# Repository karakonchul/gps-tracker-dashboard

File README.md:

# GPS Tracker Dashboard

IoT устройство за локализация със S.O.S
---

## Използвани технологии и инструменти

- **Хардуер**  
  - Arduino Nano  
  - SIM868 GSM/GPRS/GNSS модул  
  - SOS бутон
  - DWM 1000

- **Езици и фреймуъркове**  
  - C++ (Arduino скеч)  
  - JavaScript / TypeScript (Next.js + React)  
  - SQL (PostgreSQL)  

- **База данни**  
  - PostgreSQL (v17.2)  

- **Сървър и бекенд**  
  - Next.js (App Router)  
  - Node.js  
  - `pg` (node-postgres) за връзка с PostgreSQL  
  - `mqtt.js` за MQTT интеграция  

- **Фронтенд**  
  - React (вградено в Next.js)  
  - Google Maps JavaScript API  
  - Tailwind CSS за базова стилизация  

- **Реално-време**  
  - MQTT протокол, публичен брокер HiveMQ (wss://broker.hivemq.com:8884/mqtt)  

- **Тунелиране / DevOps**  
  - ngrok v3 (HTTP тунел, TCP тунел)  

---

## Предварителни условия

1. **Arduino IDE** (или друг инструмент за качване на Arduino скеч)  
2. **Node.js & npm**  
3. **PostgreSQL** (локална инсталация или изнесена чрез ngrok)  
4. **ngrok v3** (регистриран акаунт за резервация на субдомейн)  
5. **Google Maps API ключ**  

---
---

## Конфигурация на база данни (PostgreSQL)

1. Създайте база данни `gps_tracker`:
   ```sql
   CREATE DATABASE gps_tracker;

    CREATE TABLE locations (
      id SERIAL PRIMARY KEY,
      device_id VARCHAR(50) NOT NULL,
      latitude DOUBLE PRECISION NOT NULL,
      longitude DOUBLE PRECISION NOT NULL,
      timestamp TIMESTAMP DEFAULT CURRENT_TIMESTAMP
    );
    CREATE TABLE notifications (
      id SERIAL PRIMARY KEY,
      message TEXT NOT NULL,
      created_at TIMESTAMP DEFAULT CURRENT_TIMESTAMP
    );
    CREATE TABLE uwb_readings (
      id SERIAL PRIMARY KEY,
      device_id VARCHAR(50) NOT NULL,
      x DOUBLE PRECISION NOT NULL,
      y DOUBLE PRECISION NOT NULL,
      timestamp TIMESTAMP WITHOUT TIME ZONE DEFAULT CURRENT_TIMESTAMP
    );
## Геозона (Geofence) – проверка на GPS координати
   
    export function isInsideGeofence(
      latitude: number,
      longitude: number,
      centerLat = 42.6977,
      centerLon = 23.3219,
      radiusKm = 1
    ): boolean {
      const toRad = (v: number) => (v * Math.PI) / 180;
      const R = 6371; // Земен радиус в километри
  
    const dLat = toRad(centerLat - latitude);
    const dLon = toRad(centerLon - longitude);
    const a =
      Math.sin(dLat / 2) ** 2 +
      Math.cos(toRad(latitude)) *
        Math.cos(toRad(centerLat)) *
        Math.sin(dLon / 2) ** 2;
    const distance = R * 2 * Math.atan2(Math.sqrt(a), Math.sqrt(1 - a));
  
    return distance <= radiusKm;
  }

**Входни параметри**

-	**latitude, longitude** – GPS координатите на устройството.
-	**centerLat = 42.6977, centerLon = 23.3219** – координатите на центъра на геозоната (по подразбиране София).
- **radiusKm = 1**– радиусът на геозоната в километри (по подразбиране 1 км).
- **Изчисление:**
1.	Преобразуваме ширина и дължина в радиани чрез toRad.
2.	Пресмятаме разликата на ширини dLat = toRad(centerLat – latitude) и дължини dLon = toRad(centerLon – longitude).
3.	Прилагаме Haversine формулата:
 
            a = sin²(dLat/2) 
              + cos(toRad(latitude)) 
              * cos(toRad(centerLat)) 
              * sin²(dLon/2)
          
            distance = R * 2 * atan2(√a, √(1 – a))

  където R = 6371 км е земният радиус.

   4.	Ако distance ≤ radiusKm, функцията връща true (т.е. точката е вътре в геозоната). В противен случай връща false.

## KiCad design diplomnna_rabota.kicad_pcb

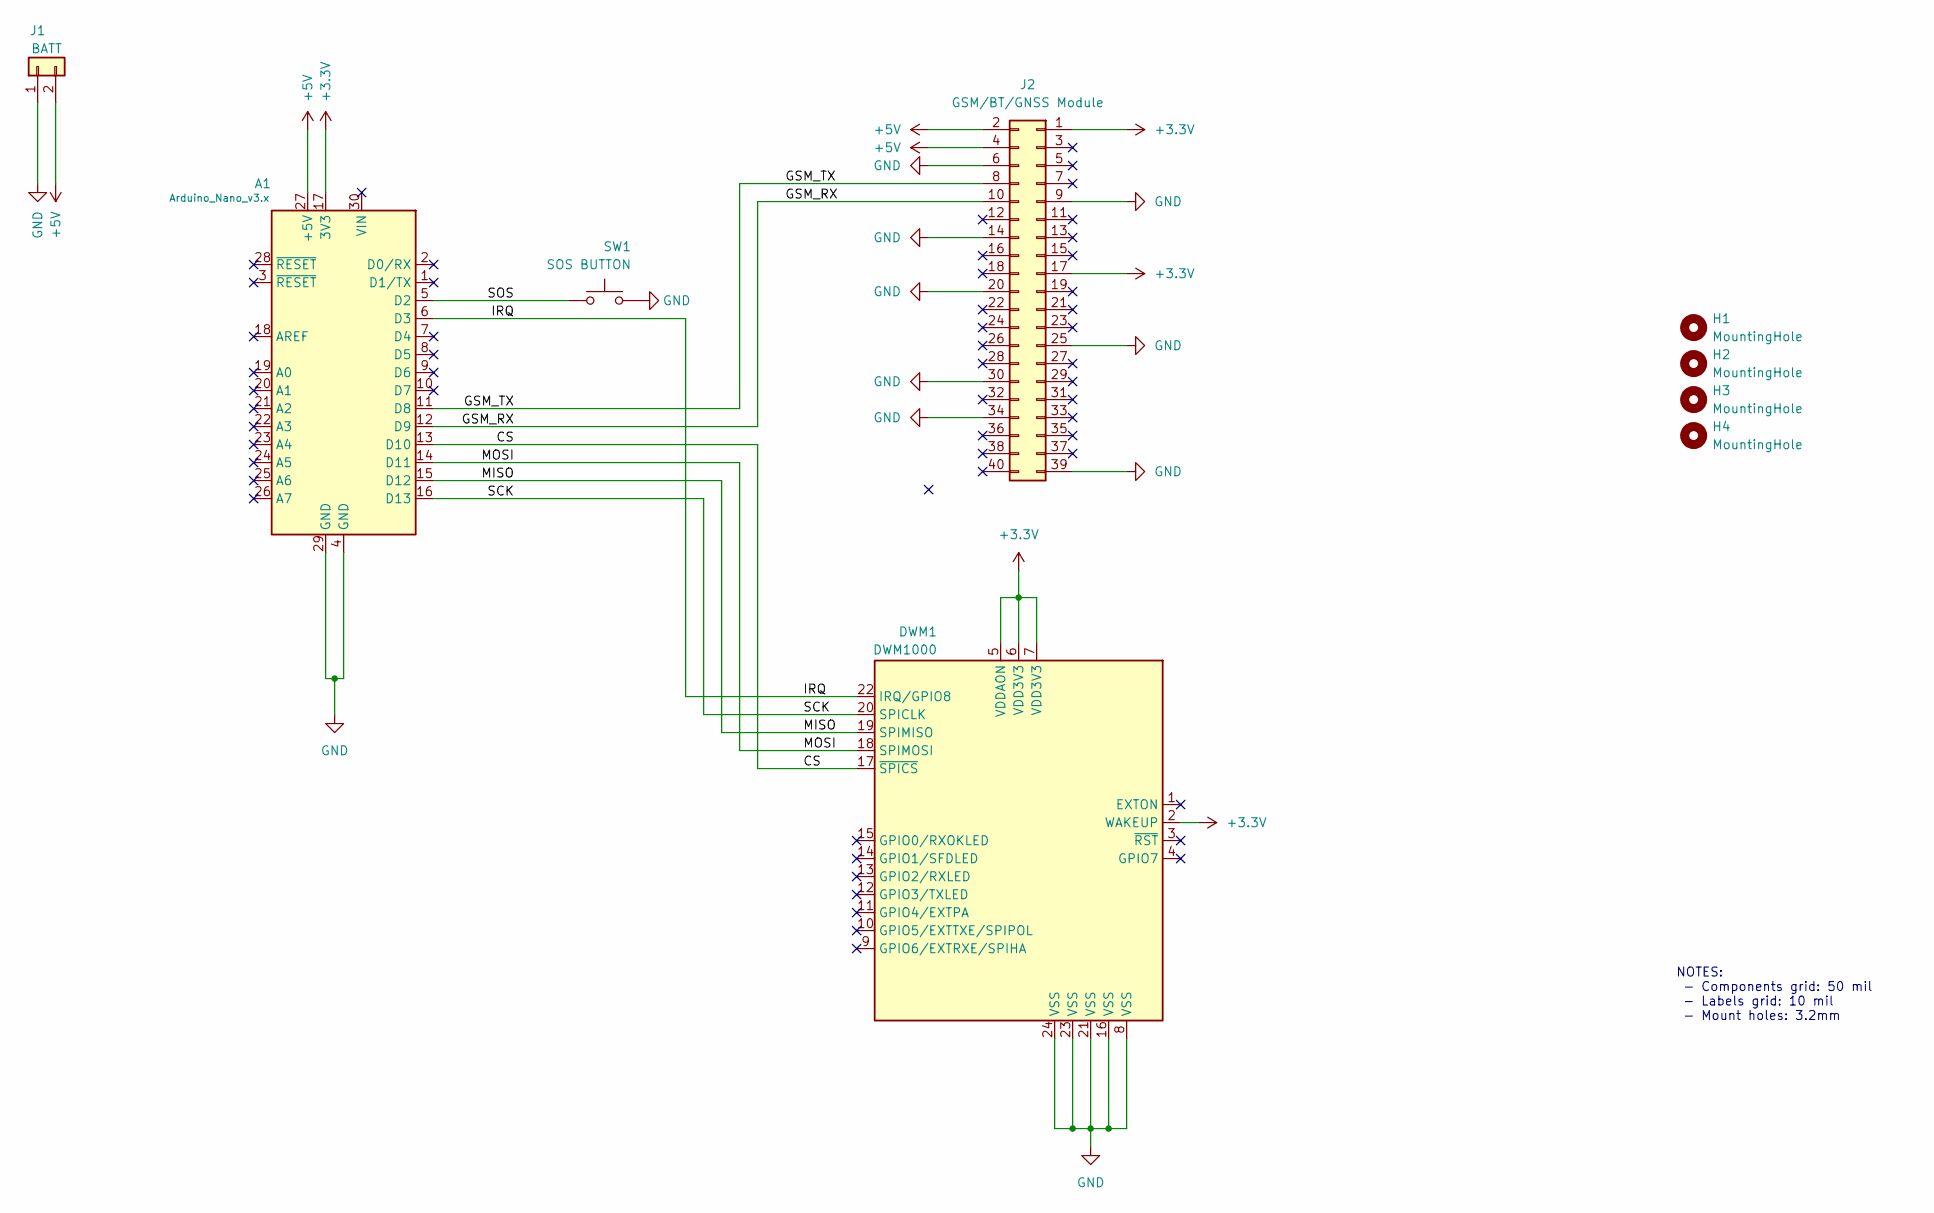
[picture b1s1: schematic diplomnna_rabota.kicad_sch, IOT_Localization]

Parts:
A1: Arduino_Nano_v3.x; Arduino_Nano
DWM1: DWM1000
H1, H2, H3, H4: MountingHole; MountingHole_3.2mm_M3
J1: BATT; Molex_KK-254_AE-6410-02A_1x02_P2.54mm_Vertical
J2: GSM/BT/GNSS Module; PinHeader_2x20_P2.54mm_Vertical
SW1: SOS BUTTON; SW_SPST_PTS647_Sx70

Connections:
+3.3V: A1.17 (3V3), DWM1.2 (WAKEUP), DWM1.5 (VDDAON), DWM1.6 (VDD3V3), DWM1.7 (VDD3V3), J2.1, J2.17
+5V: A1.27 (+5V), J1.2, J2.2, J2.4
/CS: A1.13 (D10), DWM1.17 (~SPICS)
/GSM_RX: A1.12 (D9), J2.10
/GSM_TX: A1.11 (D8), J2.8
/IRQ: A1.6 (D3), DWM1.22 (IRQ/GPIO8)
/MISO: A1.15 (D12), DWM1.19 (SPIMISO)
/MOSI: A1.14 (D11), DWM1.18 (SPIMOSI)
/SCK: A1.16 (D13), DWM1.20 (SPICLK)
/SOS: A1.5 (D2), SW1.1
GND: A1.4 (GND), A1.29 (GND), DWM1.8 (VSS), DWM1.16 (VSS), DWM1.21 (VSS), DWM1.23 (VSS), DWM1.24 (VSS), J1.1, J2.6, J2.9, J2.14, J2.20, J2.25, J2.30, J2.34, J2.39, SW1.2

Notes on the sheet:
NOTES: - Components grid: 50 mil - Labels grid: 10 mil - Mount holes: 3.2mm

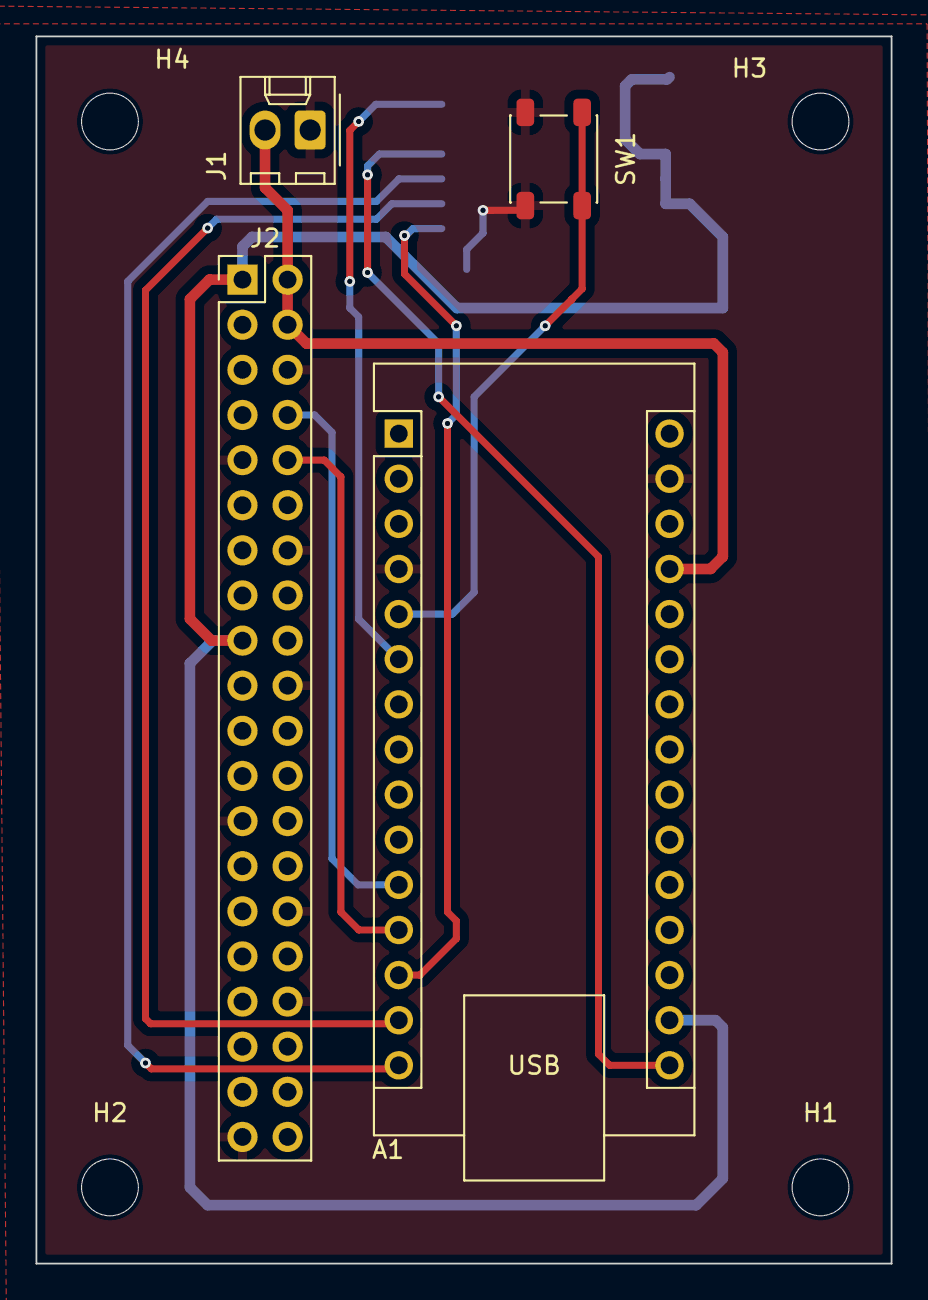
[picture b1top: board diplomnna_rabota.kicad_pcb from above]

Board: 2 copper layers, 48.1 x 69.1 mm, 9 parts (1 on the bottom side), 11 nets.

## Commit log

2025-02-07 Initial commit from Create Next App
2025-05-20 Deleted ugly icon
2025-05-20 Modified MQTT client
2025-05-20 chore: upgrade to Next.js 15.3.2 & React 19.1.0 (security fixes)
2025-05-20 New file Post end point
2025-05-20 HALF WAY
2025-05-29 updated repo
2025-06-02 arduino code
